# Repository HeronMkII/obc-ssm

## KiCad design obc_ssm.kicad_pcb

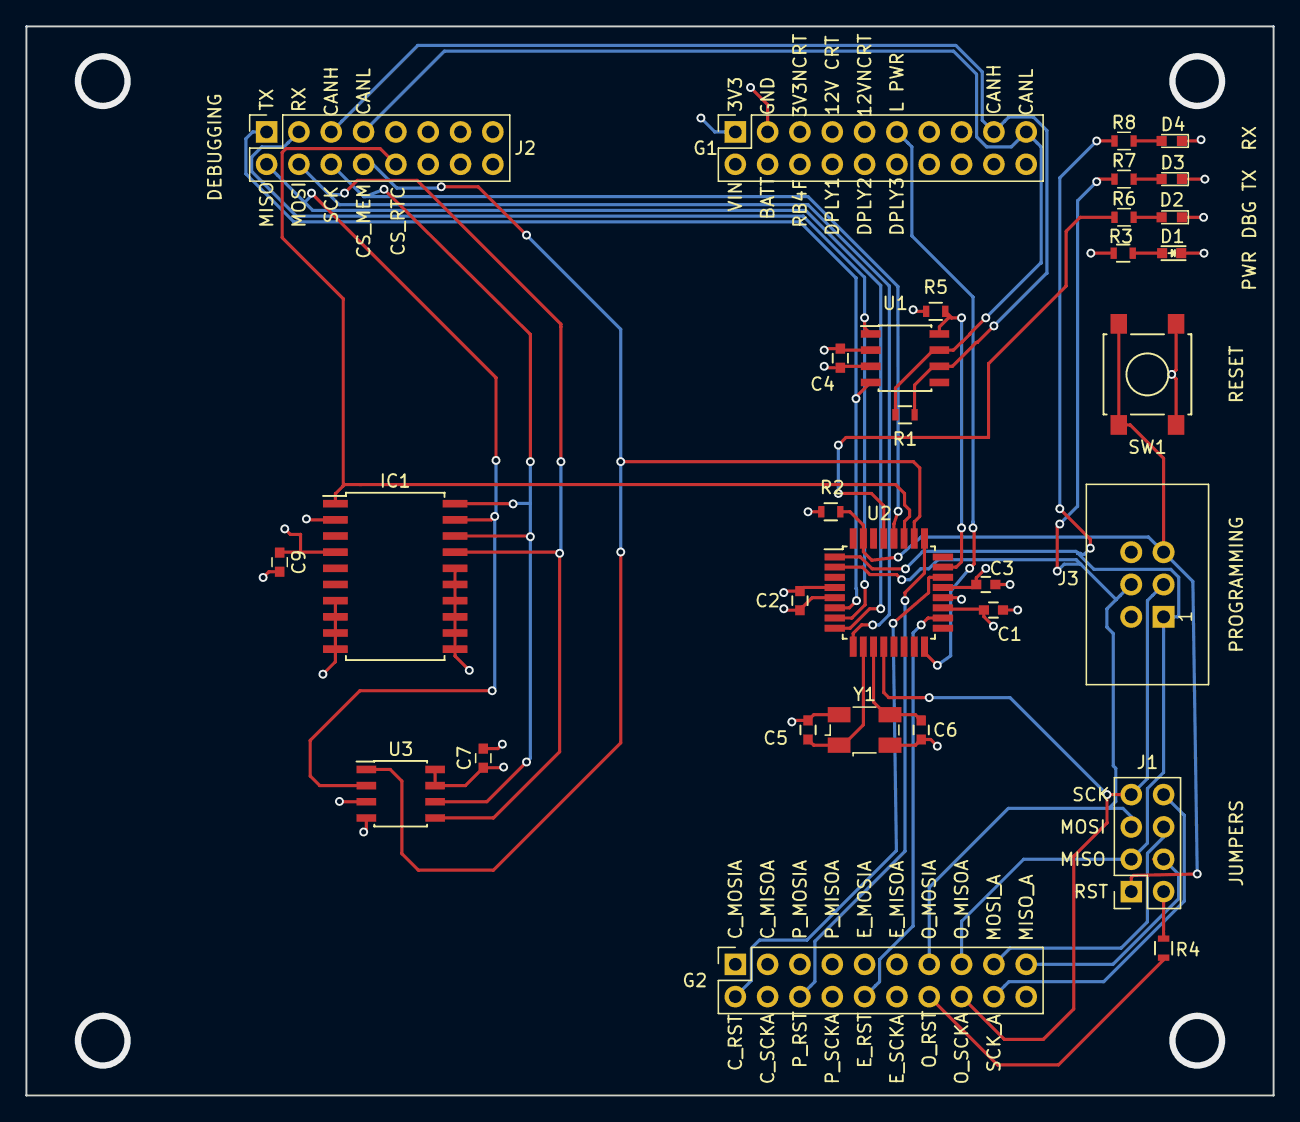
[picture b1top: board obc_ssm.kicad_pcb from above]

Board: 4 copper layers, 98.0 x 84.0 mm, 31 parts (0 on the bottom side), 32 nets.

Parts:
C1, C2, C3: 0.1 uF; C_0603
C4: 0.1uF; C_0603
C5, C6: 22pF; C_0603
C7, C9: 100nF; C_0603
D1: PWR_LED; LED_0603
D2: LED_1; LED_0603
D3: LED_TX; LED_0603
D4: LED_RX; LED_0603
G1: GENERAL CONN 1; Socket_Strip_Straight_2x10_Pitch2.54mm
G2: GENERAL CONN 2; Socket_Strip_Straight_2x10_Pitch2.54mm
IC1: DS3234; SOIC-20W_7.5x12.8mm_Pitch1.27mm
J1: RST_JMP; Socket_Strip_Straight_2x04_Pitch2.54mm
J2: DEBUG CONN; Socket_Strip_Straight_2x08_Pitch2.54mm
J3: PROGRAMMING PORT; IDC_Header_Straight_6pins
R1, R3, R4, R6, R7, R8: 120R; R_0603
R2: 10K; R_0603
R5: 1K; R_0603
SW1: SW_RST; SW_SPST_B3S-1000
U1: SN65HVD230; SOIC-8_3.9x4.9mm_Pitch1.27mm
U2: ATMEGA32M1-MU; TQFP-32_7x7mm_Pitch0.8mm
U3: SST25VF016B; SOIC-8_3.9x4.9mm_Pitch1.27mm
Y1: 8MHz; Crystal_SMD_Abracon_ABM3B-4pin_5.0x3.2mm

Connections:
+3V3: C1.2, C2.2, C3.2, C4.1, C7.1, C9.1, G1.1, IC1.4, J3.2, R2.1, R3.1, U1.3, U2.4, U2.19, U2.21, U3.3, U3.7, U3.8
/CANH: G1.17, J2.5, R1.1, U1.6
/CANL: G1.19, J2.7, R1.2, U1.7
/CAN_LPWR: R5.2, U1.8, U2.23
/COM_RST: G2.2, U2.22
/CS_MEM: J2.8, U2.26, U3.1
/CS_RTC: IC1.1, J2.10, U2.27
/EPS_RST: G2.10, U2.18
/LED1: R6.1, U2.29
/LOPWR: G1.11, U2.16
/MISO: IC1.19, J2.2, U2.8, U3.2
/MISO_A: G2.15, J1.3, J3.1, R8.1, U2.1
/MISO_A_COMMON: G2.19, J1.4
/MOSI: IC1.17, J2.4, U2.9, U3.5
/MOSI_A: G2.13, J1.5, J3.4, R7.1, U2.2
/MOSI_A_COMMON: G2.17, J1.6
/OBC_RST: G2.14, R4.1
/PAY_RST: G2.6, U2.25
/RST: J1.1, J3.5, R2.2, SW1.1, U2.31
/RX_CAN: J2.3, U1.1, U2.7
/SCK: IC1.18, IC1.20, J2.6, U2.28, U3.6
/SCK_A: G2.16, J1.7, J3.3, U2.12
/SCK_A_COMMON: G2.18, J1.8
/TX_CAN: J2.1, U1.4, U2.6
GND: C1.1, C2.1, C3.1, C4.2, C5.1, C6.1, C7.2, C9.2, D1.1, D2.1, D3.1, D4.1, G1.3, IC1.2, IC1.7, IC1.8, IC1.9, IC1.10, IC1.11, IC1.12, IC1.13, IC1.14, IC1.15, IC1.16, J3.6, R5.1, SW1.2, U1.2, U2.5, U2.20, U3.4, Y1.2, Y1.4
unnamed: C5.2, U2.10, Y1.1
unnamed: C6.2, U2.11, Y1.3
unnamed: D1.2, R3.2
unnamed: D2.2, R6.2
unnamed: D3.2, R7.2
unnamed: D4.2, R8.2
unnamed: J1.2, R4.2

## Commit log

2017-08-18 OBC Board Start
    Changed generic-ssm stuff to OBC, added flash
2017-08-19 Layout
    Almost done. just gotta make it prety
2017-08-19 Fix missing connections; DRC check passes
    Please review
2017-08-20 Mounting hole changes.
2017-08-21 Added gerber exports.
2017-09-02 Modified outputs for manufacture.
